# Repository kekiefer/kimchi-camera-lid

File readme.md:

# kimχ micro CSI Camera Lid

Hook up various Raspberry Pi-compatible cameras to your Kimchi Micro!

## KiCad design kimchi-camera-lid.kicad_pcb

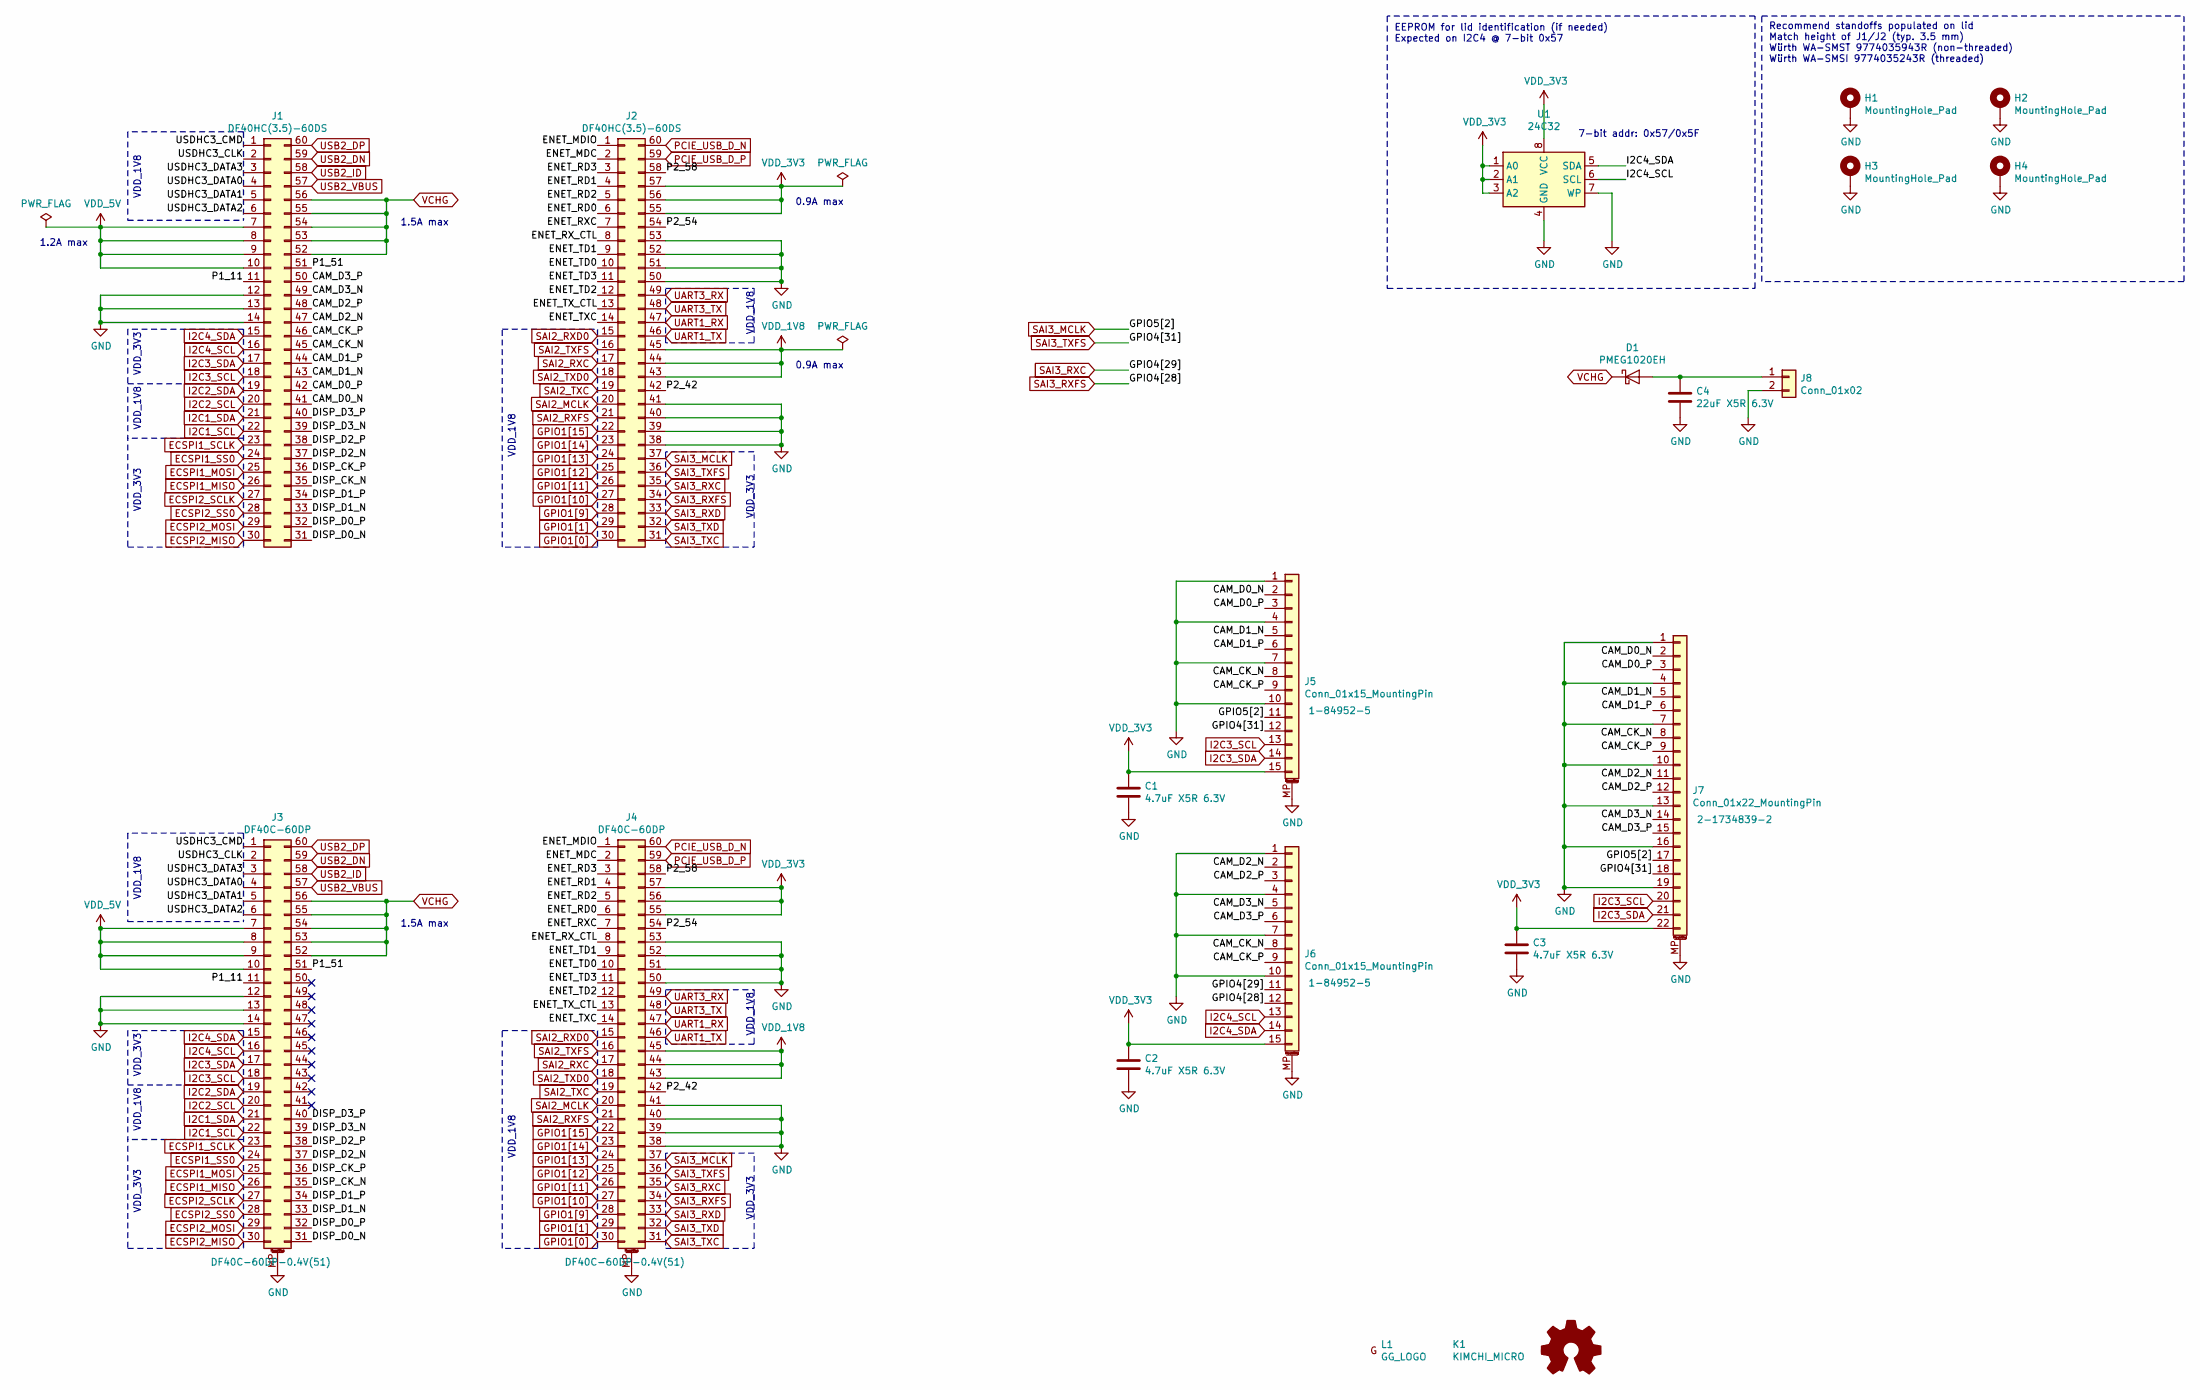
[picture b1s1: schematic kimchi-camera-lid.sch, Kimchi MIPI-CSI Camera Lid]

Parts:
C1, C2, C3: 4.7uF X5R 6.3V; C_0603_1608Metric; Mfgrpart CL10A475KQ8NNNC
C4: 22uF X5R 6.3V; C_1206_3216Metric; Mfgrpart GRT31CR60J226KE01L
D1: PMEG1020EH; D_SOD-123F; Mfgrpart PMEG1020EH,115
H1, H2, H3, H4: MountingHole_Pad; MountingHole_M2_Standoff; Mfgrpart 9774035943R
J1, J2: DF40HC(3.5)-60DS; Mfgrpart DF40HC(3.5)-60DS-0.4V(51)
J3, J4: DF40C-60DP; Mfgrpart DF40C-60DP-0.4V(51)
J5, J6: Conn_01x15_MountingPin; TE_1-84952-5_1x15-1MP_P1.0mm_Horizontal; Mfgrpart 1-84952-5
J7: Conn_01x22_MountingPin; TE_2-1734839-2_1x22-1MP_P0.5mm_Horizontal; Mfgrpart 2-1734839-2
J8: Conn_01x02; PinHeader_1x02_P2.54mm_Horizontal
K1: KIMCHI_MICRO
L1: GG_LOGO; gg-4x4
LOGO1: Logo_Open_Hardware_Small; OSHW-Logo_5.7x6mm_SilkScreen
U1: 24C32; DFN-8-1EP_3x2mm_P0.5mm_EP1.36x1.46mm; Mfgrpart M24C32-FMC6TG

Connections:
/CAM_CK_N: J1.45, J5.8, J6.8, J7.8
/CAM_CK_P: J1.46, J5.9, J6.9, J7.9
/CAM_D0_N: J1.41, J5.2, J7.2
/CAM_D0_P: J1.42, J5.3, J7.3
/CAM_D1_N: J1.43, J5.5, J7.5
/CAM_D1_P: J1.44, J5.6, J7.6
/CAM_D2_N: J1.47, J6.2, J7.11
/CAM_D2_P: J1.48, J6.3, J7.12
/CAM_D3_N: J1.49, J6.5, J7.14
/CAM_D3_P: J1.50, J6.6, J7.15
/DISP_CK_N: J1.35, J3.35
/DISP_CK_P: J1.36, J3.36
/DISP_D0_N: J1.31, J3.31
/DISP_D0_P: J1.32, J3.32
/DISP_D1_N: J1.33, J3.33
/DISP_D1_P: J1.34, J3.34
/DISP_D2_N: J1.37, J3.37
/DISP_D2_P: J1.38, J3.38
/DISP_D3_N: J1.39, J3.39
/DISP_D3_P: J1.40, J3.40
/ENET_MDC: J2.2, J4.2
/ENET_MDIO: J2.1, J4.1
/ENET_RD0: J2.6, J4.6
/ENET_RD1: J2.4, J4.4
/ENET_RD2: J2.5, J4.5
/ENET_RD3: J2.3, J4.3
/ENET_RXC: J2.7, J4.7
/ENET_RX_CTL: J2.8, J4.8
/ENET_TD0: J2.10, J4.10
/ENET_TD1: J2.9, J4.9
/ENET_TD2: J2.12, J4.12
/ENET_TD3: J2.11, J4.11
/ENET_TXC: J2.14, J4.14
/ENET_TX_CTL: J2.13, J4.13
/P1_11: J1.11, J3.11
/P1_51: J1.51, J3.51
/P2_42: J2.42, J4.42
/P2_54: J2.54, J4.54
/P2_58: J2.58, J4.58
/USDHC3_CLK: J1.2, J3.2
/USDHC3_CMD: J1.1, J3.1
/USDHC3_DATA0: J1.4, J3.4
/USDHC3_DATA1: J1.5, J3.5
/USDHC3_DATA2: J1.6, J3.6
/USDHC3_DATA3: J1.3, J3.3
ECSPI1_MISO: J1.26, J3.26
ECSPI1_MOSI: J1.25, J3.25
ECSPI1_SCLK: J1.23, J3.23
ECSPI1_SS0: J1.24, J3.24
ECSPI2_MISO: J1.30, J3.30
ECSPI2_MOSI: J1.29, J3.29
ECSPI2_SCLK: J1.27, J3.27
ECSPI2_SS0: J1.28, J3.28
GND: C1.2, C2.2, C3.2, C4.2, H1.1, H2.1, H3.1, H4.1, J1.12, J1.13, J1.14, J2.38, J2.39, J2.40, J2.41, J2.50, J2.51, J2.52, J2.53, J3.12, J3.13, J3.14, J3.MP (MountPin), J4.38, J4.39, J4.40, J4.41, J4.50, J4.51, J4.52, J4.53, J4.MP (MountPin), J5.1, J5.4, J5.7, J5.10, J5.MP (MountPin), J6.1, J6.4, J6.7, J6.10, J6.MP (MountPin), J7.1, J7.4, J7.7, J7.10, J7.13, J7.16, J7.19, J7.MP (MountPin), J8.2, U1.4 (GND), U1.7 (WP)
GPIO1[0]: J2.30, J4.30
GPIO1[1]: J2.29, J4.29
GPIO1[9]: J2.28, J4.28
GPIO1[10]: J2.27, J4.27
GPIO1[11]: J2.26, J4.26
GPIO1[12]: J2.25, J4.25
GPIO1[13]: J2.24, J4.24
GPIO1[14]: J2.23, J4.23
GPIO1[15]: J2.22, J4.22
I2C1_SCL: J1.22, J3.22
I2C1_SDA: J1.21, J3.21
I2C2_SCL: J1.20, J3.20
I2C2_SDA: J1.19, J3.19
I2C3_SCL: J1.18, J3.18, J5.13, J7.20
I2C3_SDA: J1.17, J3.17, J5.14, J7.21
I2C4_SCL: J1.16, J3.16, J6.13, U1.6 (SCL)
I2C4_SDA: J1.15, J3.15, J6.14, U1.5 (SDA)
unnamed: C4.1, D1.2 (A), J8.1
PCIE_USB_D_N: J2.60, J4.60
PCIE_USB_D_P: J2.59, J4.59
SAI2_MCLK: J2.20, J4.20
SAI2_RXC: J2.17, J4.17
SAI2_RXD0: J2.15, J4.15
SAI2_RXFS: J2.21, J4.21
SAI2_TXC: J2.19, J4.19
SAI2_TXD0: J2.18, J4.18
SAI2_TXFS: J2.16, J4.16
SAI3_MCLK: J2.37, J4.37, J5.11, J7.17
SAI3_RXC: J2.35, J4.35, J6.11
SAI3_RXD: J2.33, J4.33
SAI3_RXFS: J2.34, J4.34, J6.12
SAI3_TXC: J2.31, J4.31
SAI3_TXD: J2.32, J4.32
SAI3_TXFS: J2.36, J4.36, J5.12, J7.18
UART1_RX: J2.47, J4.47
UART1_TX: J2.46, J4.46
UART3_RX: J2.49, J4.49
UART3_TX: J2.48, J4.48
USB2_DN: J1.59, J3.59
USB2_DP: J1.60, J3.60
USB2_ID: J1.58, J3.58
USB2_VBUS: J1.57, J3.57
VCHG: D1.1 (K), J1.52, J1.53, J1.54, J1.55, J1.56, J3.52, J3.53, J3.54, J3.55, J3.56
VDD_1V8: J2.43, J2.44, J2.45, J4.43, J4.44, J4.45
VDD_3V3: C1.1, C2.1, C3.1, J2.55, J2.56, J2.57, J4.55, J4.56, J4.57, J5.15, J6.15, J7.22, U1.1 (A0), U1.2 (A1), U1.3 (A2), U1.8 (VCC)
VDD_5V: J1.7, J1.8, J1.9, J1.10, J3.7, J3.8, J3.9, J3.10

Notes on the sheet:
7-bit addr: 0x57/0x5F
VDD_1V8
VDD_3V3
1.2A max
0.9A max
1.5A max
EEPROM for lid identification (if needed) Expected on I2C4 @ 7-bit 0x57
Recommend standoffs populated on lid Match height of J1/J2 (typ. 3.5 mm) Würth WA-SMST 9774035943R (non-threaded) Würth WA-SMSI 9774035243R (threaded)

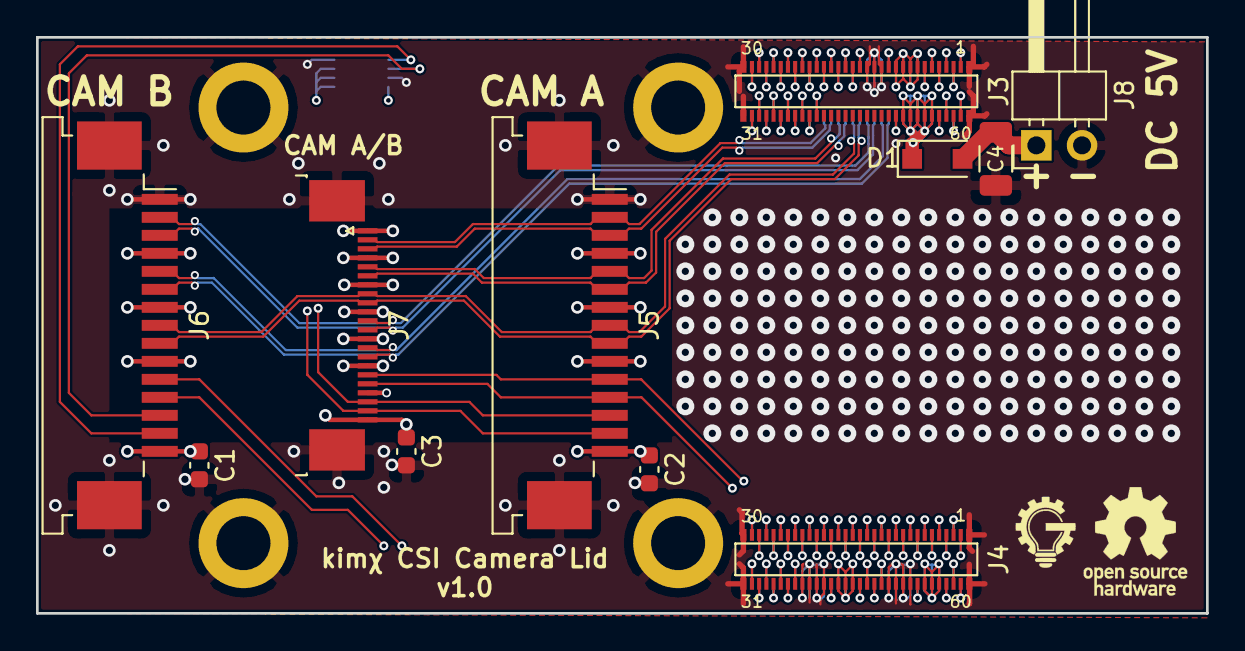
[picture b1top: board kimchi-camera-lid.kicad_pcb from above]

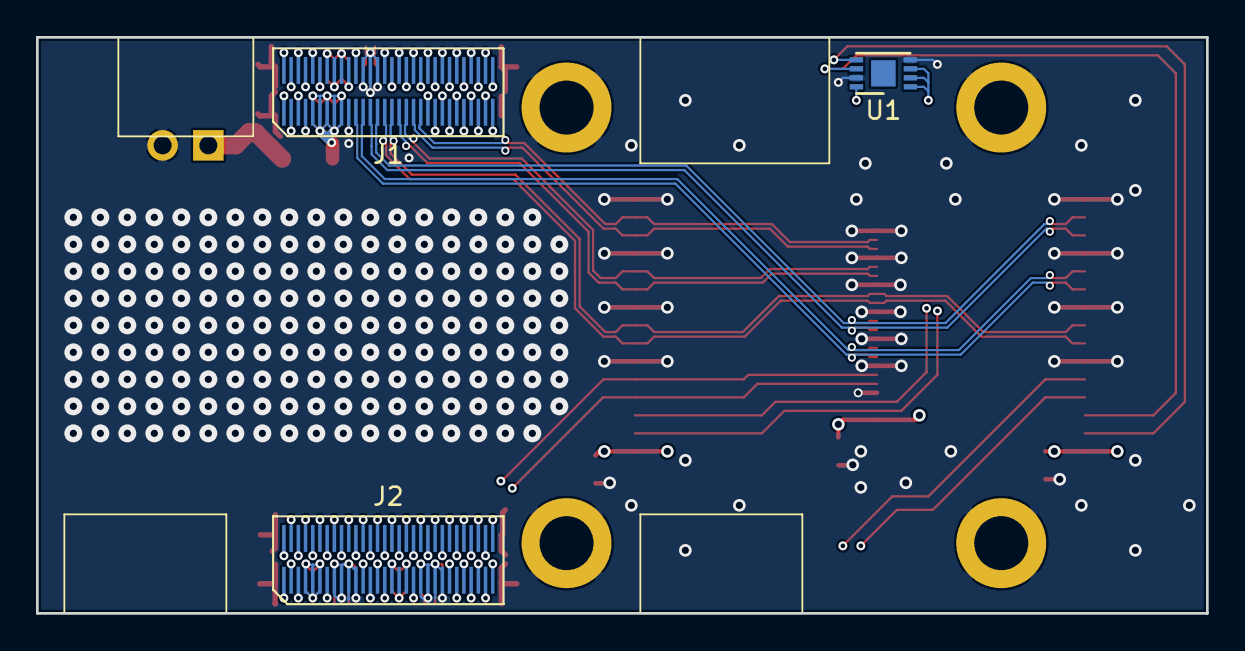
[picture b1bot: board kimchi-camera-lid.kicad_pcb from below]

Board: 4 copper layers, 65.0 x 32.0 mm, 21 parts (8 on the bottom side), 100 nets.

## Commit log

2021-07-28 Initial commit of CSI camera lid
2021-08-03 Complete design for v1.0
2021-08-10 Increase 0.2/0.4 mm via to 0.25/0.5 mm
